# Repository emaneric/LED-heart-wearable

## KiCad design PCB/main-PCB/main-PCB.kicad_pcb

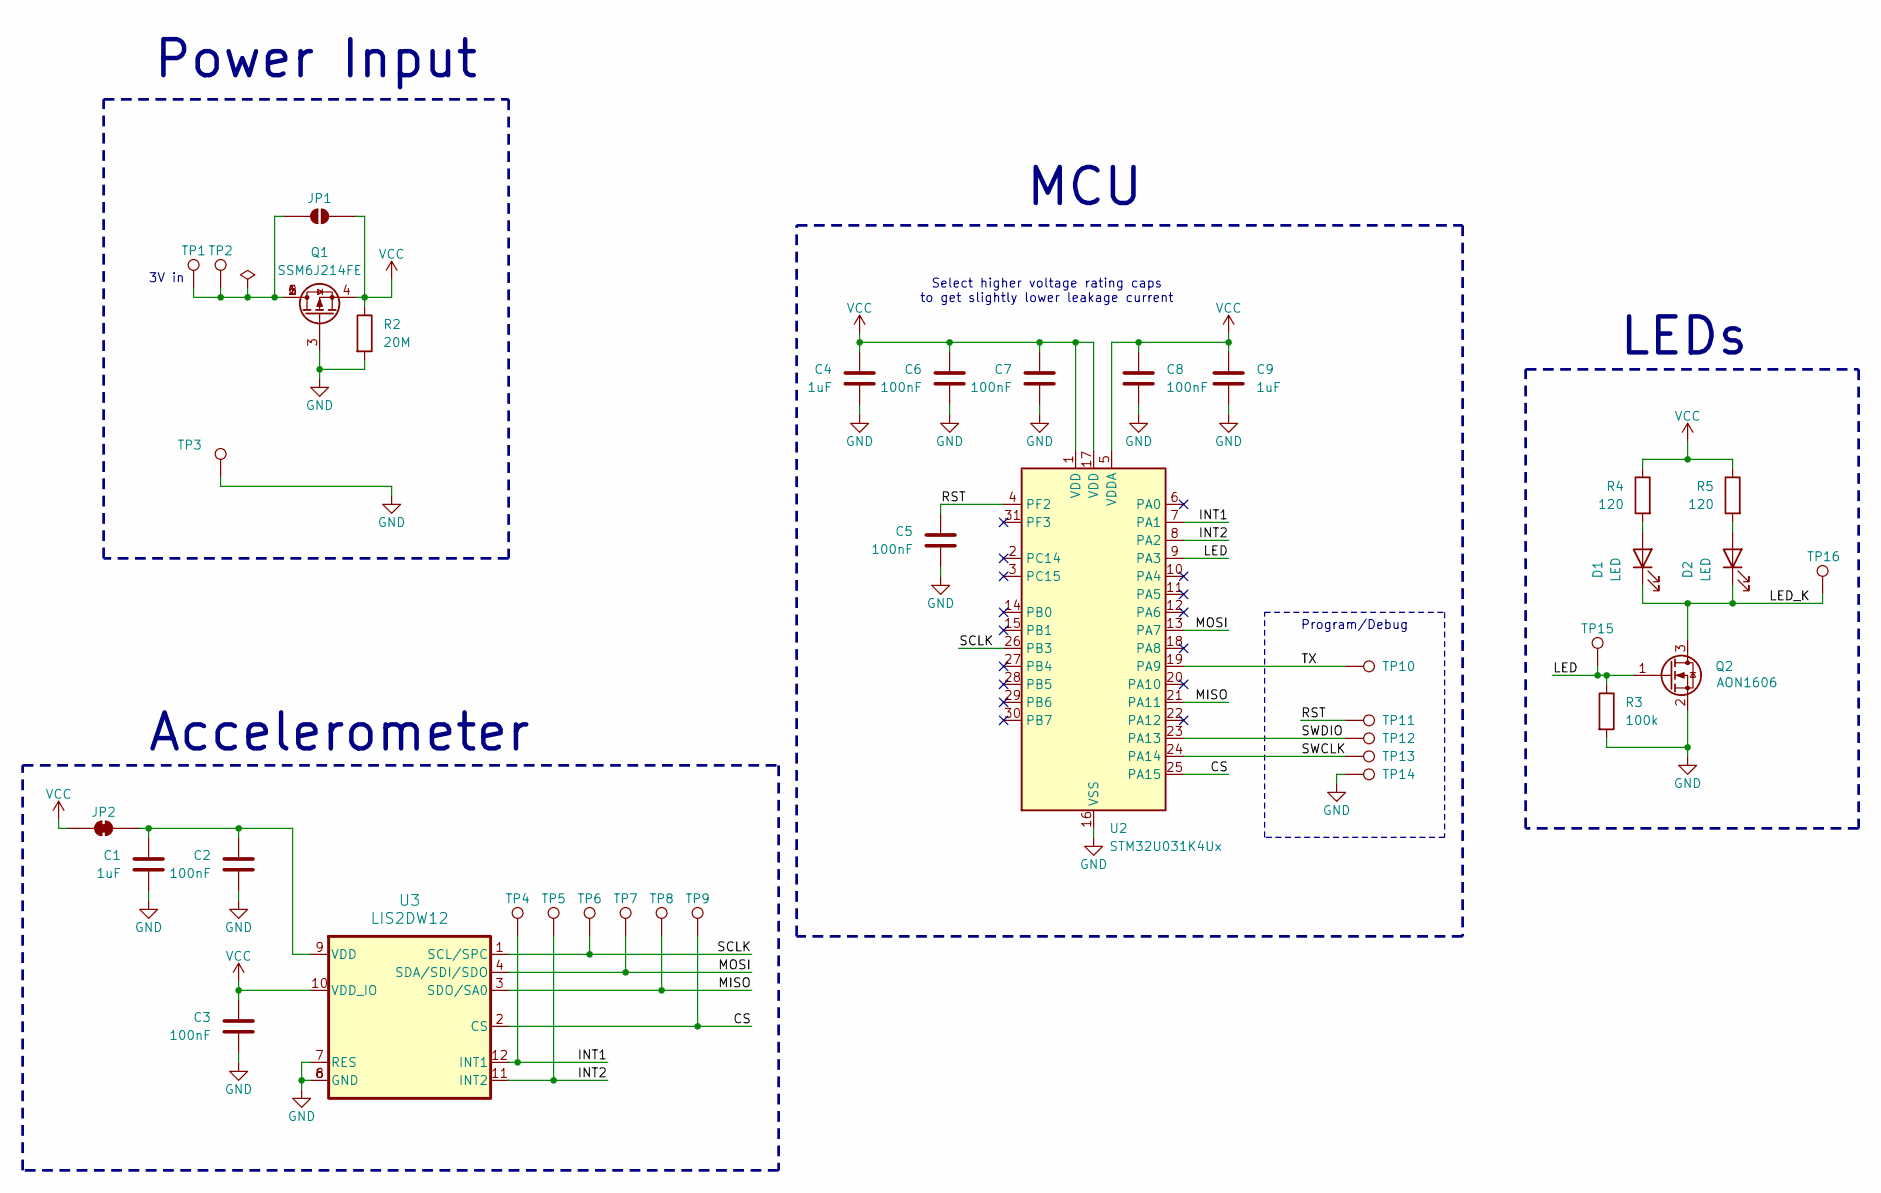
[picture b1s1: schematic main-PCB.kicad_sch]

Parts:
C1, C4, C9: 1uF; C_0603_1608Metric
C2, C3, C5, C6, C7, C8: 100nF; C_0402_1005Metric
D1, D2: LED; LED_0402_1005Metric
JP1: SolderJumper_2_Open; SolderJumper-2_P1.3mm_Open_RoundedPad1.0x1.5mm
JP2: SolderJumper_2_Bridged; SolderJumper-2_P1.3mm_Bridged_RoundedPad1.0x1.5mm
Q1: SSM6J214FE; SOT-563
Q2: Q_NMOS_GSD; Diodes_DFN1006-3; MPN AON1606
R2: 20M; R_0402_1005Metric
R3: 100k; R_0402_1005Metric
R4, R5: 120; R_0402_1005Metric
TP1, TP16: TestPoint; YZ00515045R-07
TP2, TP10, TP11, TP12, TP13, TP14: TestPoint; TestPoint_Pad_D1.0mm
TP3: TestPoint; YZ110715020R-01
TP4, TP5, TP6, TP7, TP8, TP9, TP15: TestPoint; TestPoint_Pad_D0.5mm
U2: STM32U031K4Ux; QFN-32-1EP_5x5mm_P0.5mm_EP3.45x3.45mm; MPN STM32U031K4U6
U3: LIS2DW12

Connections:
/CS: TP9.1 (1_1), U2.25 (PA15), U3.2 (CS)
/INT1: TP4.1 (1_1), U2.7 (PA1), U3.12 (INT1)
/INT2: TP5.1 (1_1), U2.8 (PA2), U3.11 (INT2)
/LED: Q2.1 (G), R3.1, TP15.1 (1_1), U2.9 (PA3)
/LED_K: D1.1 (K), D2.1 (K), Q2.3 (D), TP16.1 (1_1)
/MISO: TP8.1 (1_1), U2.21 (PA11), U3.3 (SDO/SA0)
/MOSI: TP7.1 (1_1), U2.13 (PA7), U3.4 (SDA/SDI/SDO)
/RST: C5.1, TP11.1 (1_1), U2.4 (PF2)
/SCLK: TP6.1 (1_1), U2.26 (PB3), U3.1 (SCL/SPC)
/SWCLK: TP13.1 (1_1), U2.24 (PA14)
/SWDIO: TP12.1 (1_1), U2.23 (PA13)
/TX: TP10.1 (1_1), U2.19 (PA9)
GND: C1.2, C2.2, C3.2, C4.2, C5.2, C6.2, C7.2, C8.2, C9.2, Q1.3 (G), Q2.2 (S), R2.2, R3.2, TP3.1 (1_1), TP14.1 (1_1), U2.16 (VSS), U2.32 (VSS), U2.33 (VSS), U3.6 (GND), U3.7 (RES), U3.8 (GND)
unnamed: D1.2 (A), R4.2
unnamed: D2.2 (A), R5.2
unnamed: JP1.1 (A), Q1.1 (D), Q1.2 (D), Q1.5 (D), Q1.6 (D), TP1.1 (1_1), TP2.1 (1_1)
unnamed: C1.1, C2.1, JP2.2 (B), U3.9 (VDD)
VCC: C3.1, C4.1, C6.1, C7.1, C8.1, C9.1, JP1.2 (B), JP2.1 (A), Q1.4 (S), R2.1, R4.1, R5.1, U2.1 (VDD), U2.5 (VDDA), U2.17 (VDD), U3.10 (VDD_IO)

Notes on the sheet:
LEDs
MCU
Power Input
Select higher voltage rating caps to get slightly lower leakage current
3V in
Accelerometer
Program/Debug

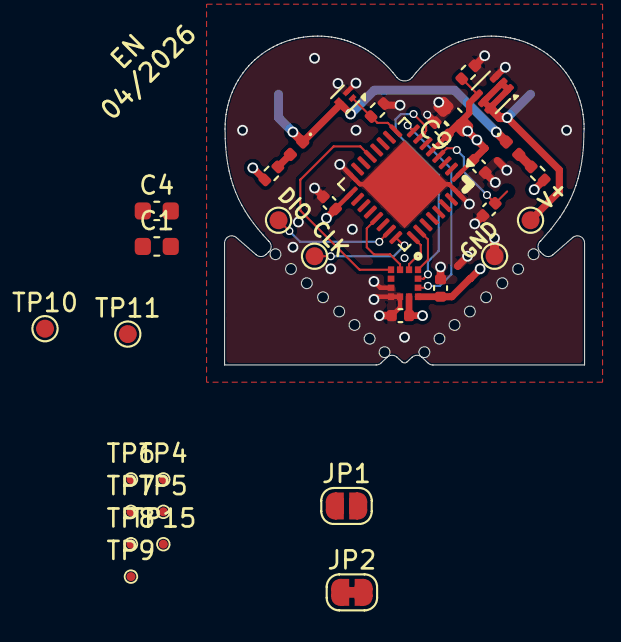
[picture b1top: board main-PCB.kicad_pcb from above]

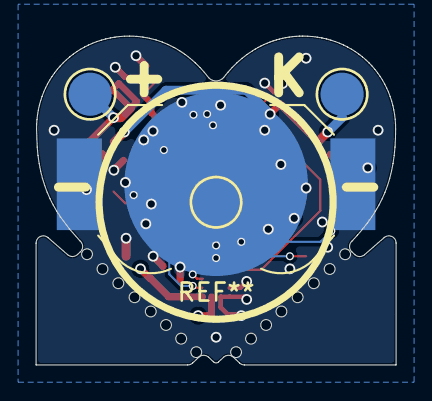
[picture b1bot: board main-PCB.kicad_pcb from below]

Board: 4 copper layers, 20.0 x 18.3 mm, 37 parts (3 on the bottom side), 18 nets.

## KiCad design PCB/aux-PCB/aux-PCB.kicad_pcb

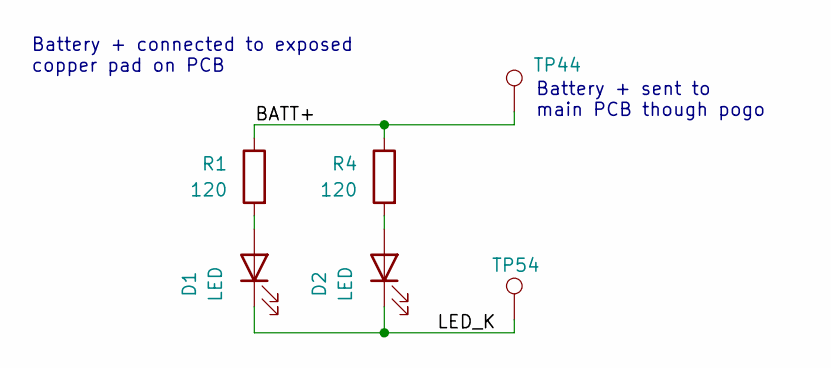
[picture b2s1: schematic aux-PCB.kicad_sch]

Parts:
D1, D2: LED; LED_0402_1005Metric
R1, R4: 120; R_0402_1005Metric
TP44, TP54: TestPoint; TestPoint_Pad_D2.0mm

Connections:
/BATT+: R1.1, R4.1, TP44.1 (1_1)
/LED_K: D1.1 (K), D2.1 (K), TP54.1 (1_1)
unnamed: D1.2 (A), R1.2
unnamed: D2.2 (A), R4.2

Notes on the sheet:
Battery + sent to main PCB though pogo
Battery + connected to exposed copper pad on PCB

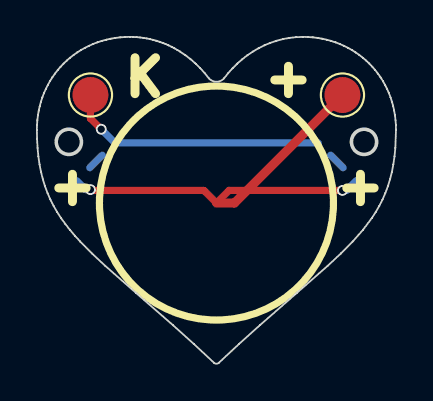
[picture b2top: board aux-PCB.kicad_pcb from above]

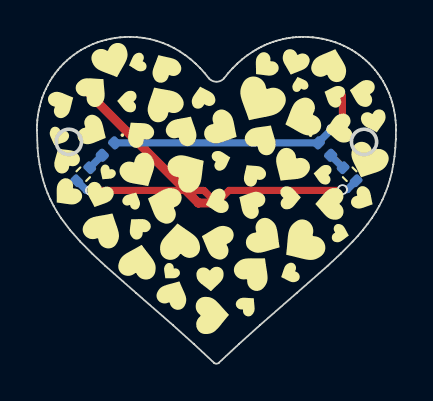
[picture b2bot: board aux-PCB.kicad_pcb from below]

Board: 2 copper layers, 19.8 x 18.1 mm, 6 parts (4 on the bottom side), 4 nets.

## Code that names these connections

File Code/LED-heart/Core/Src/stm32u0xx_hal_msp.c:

/* USER CODE BEGIN Header */
/**
  ******************************************************************************
  * @file         stm32u0xx_hal_msp.c
  * @brief        This file provides code for the MSP Initialization
  *               and de-Initialization codes.
  ******************************************************************************
  * @attention
  *
  * Copyright (c) 2026 STMicroelectronics.
  * All rights reserved.
  *
  * This software is licensed under terms that can be found in the LICENSE file
  * in the root directory of this software component.
  * If no LICENSE file comes with this software, it is provided AS-IS.
  *
  ******************************************************************************
  */
/* USER CODE END Header */
/* Includes ------------------------------------------------------------------*/
#include "main.h"
/* USER CODE BEGIN Includes */

/* USER CODE END Includes */

/* Private typedef -----------------------------------------------------------*/
/* USER CODE BEGIN TD */

/* USER CODE END TD */

/* Private define ------------------------------------------------------------*/
/* USER CODE BEGIN Define */

/* USER CODE END Define */

/* Private macro -------------------------------------------------------------*/
/* USER CODE BEGIN Macro */

/* USER CODE END Macro */

/* Private variables ---------------------------------------------------------*/
/* USER CODE BEGIN PV */

/* USER CODE END PV */

/* Private function prototypes -----------------------------------------------*/
/* USER CODE BEGIN PFP */

/* USER CODE END PFP */

/* External functions --------------------------------------------------------*/
/* USER CODE BEGIN ExternalFunctions */

/* USER CODE END ExternalFunctions */

/* USER CODE BEGIN 0 */

/* USER CODE END 0 */

void HAL_TIM_MspPostInit(TIM_HandleTypeDef *htim);
                    /**
  * Initializes the Global MSP.
  */
void HAL_MspInit(void)
{

  /* USER CODE BEGIN MspInit 0 */

  /* USER CODE END MspInit 0 */

  __HAL_RCC_PWR_CLK_ENABLE();
  __HAL_RCC_SYSCFG_CLK_ENABLE();

  /* System interrupt init*/

  /* USER CODE BEGIN MspInit 1 */

  /* USER CODE END MspInit 1 */
}

/**
  * @brief RTC MSP Initialization
  * This function configures the hardware resources used in this example
  * @param hrtc: RTC handle pointer
  * @retval None
  */
void HAL_RTC_MspInit(RTC_HandleTypeDef* hrtc)
{
  RCC_PeriphCLKInitTypeDef PeriphClkInit = {0};
  if(hrtc->Instance==RTC)
  {
    /* USER CODE BEGIN RTC_MspInit 0 */

    /* USER CODE END RTC_MspInit 0 */

  /** Initializes the peripherals clocks
  */
    PeriphClkInit.PeriphClockSelection = RCC_PERIPHCLK_RTC;
    PeriphClkInit.RTCClockSelection = RCC_RTCCLKSOURCE_LSI;
    if (HAL_RCCEx_PeriphCLKConfig(&PeriphClkInit) != HAL_OK)
    {
      Error_Handler();
    }

    /* Peripheral clock enable */
    __HAL_RCC_RTC_ENABLE();
    __HAL_RCC_RTCAPB_CLK_ENABLE();
    /* RTC interrupt Init */
    HAL_NVIC_SetPriority(RTC_TAMP_IRQn, 0, 0);
    HAL_NVIC_EnableIRQ(RTC_TAMP_IRQn);
    /* USER CODE BEGIN RTC_MspInit 1 */

    /* USER CODE END RTC_MspInit 1 */

  }

}

/**
  * @brief RTC MSP De-Initialization
  * This function freeze the hardware resources used in this example
  * @param hrtc: RTC handle pointer
  * @retval None
  */
void HAL_RTC_MspDeInit(RTC_HandleTypeDef* hrtc)
{
  if(hrtc->Instance==RTC)
  {
    /* USER CODE BEGIN RTC_MspDeInit 0 */

    /* USER CODE END RTC_MspDeInit 0 */
    /* Peripheral clock disable */
    __HAL_RCC_RTC_DISABLE();
    __HAL_RCC_RTCAPB_CLK_DISABLE();

    /* RTC interrupt DeInit */
    HAL_NVIC_DisableIRQ(RTC_TAMP_IRQn);
    /* USER CODE BEGIN RTC_MspDeInit 1 */

    /* USER CODE END RTC_MspDeInit 1 */
  }

}

/**
  * @brief SPI MSP Initialization
  * This function configures the hardware resources used in this example
  * @param hspi: SPI handle pointer
  * @retval None
  */
void HAL_SPI_MspInit(SPI_HandleTypeDef* hspi)
{
  GPIO_InitTypeDef GPIO_InitStruct = {0};
  if(hspi->Instance==SPI1)
  {
    /* USER CODE BEGIN SPI1_MspInit 0 */

    /* USER CODE END SPI1_MspInit 0 */
    /* Peripheral clock enable */
    __HAL_RCC_SPI1_CLK_ENABLE();

    __HAL_RCC_GPIOA_CLK_ENABLE();
    __HAL_RCC_GPIOB_CLK_ENABLE();
    /**SPI1 GPIO Configuration
    PA7     ------> SPI1_MOSI
    PA11 [PA9]     ------> SPI1_MISO
    PB3     ------> SPI1_SCK
    */
    GPIO_InitStruct.Pin = GPIO_PIN_7|GPIO_PIN_11;
    GPIO_InitStruct.Mode = GPIO_MODE_AF_PP;
    GPIO_InitStruct.Pull = GPIO_NOPULL;
    GPIO_InitStruct.Speed = GPIO_SPEED_FREQ_LOW;
    GPIO_InitStruct.Alternate = GPIO_AF5_SPI1;
    HAL_GPIO_Init(GPIOA, &GPIO_InitStruct);

    GPIO_InitStruct.Pin = GPIO_PIN_3;
    GPIO_InitStruct.Mode = GPIO_MODE_AF_PP;
    GPIO_InitStruct.Pull = GPIO_PULLDOWN;
    GPIO_InitStruct.Speed = GPIO_SPEED_FREQ_LOW;
    GPIO_InitStruct.Alternate = GPIO_AF5_SPI1;
    HAL_GPIO_Init(GPIOB, &GPIO_InitStruct);

    /* SPI1 interrupt Init */
    HAL_NVIC_SetPriority(SPI1_IRQn, 0, 0);
    HAL_NVIC_EnableIRQ(SPI1_IRQn);
    /* USER CODE BEGIN SPI1_MspInit 1 */

    /* USER CODE END SPI1_MspInit 1 */

  }

}

/**
  * @brief SPI MSP De-Initialization
  * This function freeze the hardware resources used in this example
  * @param hspi: SPI handle pointer
  * @retval None
  */
void HAL_SPI_MspDeInit(SPI_HandleTypeDef* hspi)
{
  if(hspi->Instance==SPI1)
  {
    /* USER CODE BEGIN SPI1_MspDeInit 0 */

    /* USER CODE END SPI1_MspDeInit 0 */
    /* Peripheral clock disable */
    __HAL_RCC_SPI1_CLK_DISABLE();

    /**SPI1 GPIO Configuration
    PA7     ------> SPI1_MOSI
    PA11 [PA9]     ------> SPI1_MISO
    PB3     ------> SPI1_SCK
    */
    HAL_GPIO_DeInit(GPIOA, GPIO_PIN_7|GPIO_PIN_11);

    HAL_GPIO_DeInit(GPIOB, GPIO_PIN_3);

    /* SPI1 interrupt DeInit */
    HAL_NVIC_DisableIRQ(SPI1_IRQn);
    /* USER CODE BEGIN SPI1_MspDeInit 1 */

    /* USER CODE END SPI1_MspDeInit 1 */
  }

}

/**
  * @brief TIM_PWM MSP Initialization
  * This function configures the hardware resources used in this example
  * @param htim_pwm: TIM_PWM handle pointer
  * @retval None
  */
void HAL_TIM_PWM_MspInit(TIM_HandleTypeDef* htim_pwm)
{
  if(htim_pwm->Instance==TIM2)
  {
    /* USER CODE BEGIN TIM2_MspInit 0 */

    /* USER CODE END TIM2_MspInit 0 */
    /* Peripheral clock enable */
    __HAL_RCC_TIM2_CLK_ENABLE();
    /* USER CODE BEGIN TIM2_MspInit 1 */

    /* USER CODE END TIM2_MspInit 1 */

  }

}

void HAL_TIM_MspPostInit(TIM_HandleTypeDef* htim)
{
  GPIO_InitTypeDef GPIO_InitStruct = {0};
  if(htim->Instance==TIM2)
  {
    /* USER CODE BEGIN TIM2_MspPostInit 0 */

    /* USER CODE END TIM2_MspPostInit 0 */

    __HAL_RCC_GPIOA_CLK_ENABLE();
    /**TIM2 GPIO Configuration
    PA3     ------> TIM2_CH4
    */
    GPIO_InitStruct.Pin = GPIO_PIN_3;
    GPIO_InitStruct.Mode = GPIO_MODE_AF_PP;
    GPIO_InitStruct.Pull = GPIO_NOPULL;
    GPIO_InitStruct.Speed = GPIO_SPEED_FREQ_LOW;
    GPIO_InitStruct.Alternate = GPIO_AF1_TIM2;
    HAL_GPIO_Init(GPIOA, &GPIO_InitStruct);

    /* USER CODE BEGIN TIM2_MspPostInit 1 */

    /* USER CODE END TIM2_MspPostInit 1 */
  }

}
/**
  * @brief TIM_PWM MSP De-Initialization
  * This function freeze the hardware resources used in this example
  * @param htim_pwm: TIM_PWM handle pointer
  * @retval None
  */
void HAL_TIM_PWM_MspDeInit(TIM_HandleTypeDef* htim_pwm)
{
  if(htim_pwm->Instance==TIM2)
  {
    /* USER CODE BEGIN TIM2_MspDeInit 0 */

    /* USER CODE END TIM2_MspDeInit 0 */
    /* Peripheral clock disable */
    __HAL_RCC_TIM2_CLK_DISABLE();
    /* USER CODE BEGIN TIM2_MspDeInit 1 */

    /* USER CODE END TIM2_MspDeInit 1 */
  }

}

/* USER CODE BEGIN 1 */

/* USER CODE END 1 */

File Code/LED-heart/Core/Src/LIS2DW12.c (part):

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    status = LIS2DW12_write_register(hspi, LIS2DW12_REG_FIFO_CTRL, FIFO_CTRL_reg.raw);
    HAL_Delay(1);

    //Route the FIFO threshold interrupt to the INT2 pad (accelerometer INT2 -> PA2)
    CTRL5_INT2_PAD_reg.field.INT2_FTH = 1;
    status = LIS2DW12_write_register(hspi, LIS2DW12_REG_CTRL5_INT2_PAD, CTRL5_INT2_PAD_reg.raw);
    HAL_Delay(1);
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    //600 ms here was less than a single sample, so the transient was still in flight when
    //the threshold was armed. INT1 then came up immediately, and because WKUP3 is
    //level-triggered the MCU woke straight back out of Shutdown. 2000 ms is 3.2 periods.
    //The caller still confirms INT1 is actually low before arming the wake pin, so this
    //delay no longer has to be exactly right - it just has to get most of the way there.
    HAL_Delay(LIS2DW12_SLEEP_SETTLE_MS);

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    error |= (LIS2DW12_write_register(hspi, LIS2DW12_REG_CTRL3, CTRL3_reg.raw) != HAL_OK);
    HAL_Delay(1);

    //Route wake-up recognition to the INT1 pad (accelerometer INT1 -> PA1 wake pin).
    //On the LIS2DW12 the wake-up event can only be routed to INT1.
    CTRL4_INT1_PAD_reg.field.INT1_WU = 1;
    error |= (LIS2DW12_write_register(hspi, LIS2DW12_REG_CTRL4_INT1_PAD, CTRL4_INT1_PAD_reg.raw) != HAL_OK);
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
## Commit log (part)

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2026-03-04 -Added custom silkscreen -Generated gerbers -Exported STEP files
2026-03-15 -Updated STEP files
2026-03-28 -Updated MCU part number -Changed to 0402 passives
2026-05-04 Updated PCB STEP file
2026-05-04 Updated gitignore
2026-06-07 -STarted working in accelerometer driver
2026-06-11 Initial work on LIS2DU12 driver
2026-06-17 -Added initial read of acceleration data
2026-06-23 Refactor LIS2DU12 driver: update read_FIFO function to include FIFO length and acceleration data array; modify read_register function parameter name; adjust FIFO watermark to 25 samples; enhance main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
